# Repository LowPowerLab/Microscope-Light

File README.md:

# Microscope-Light
### Simple wireless ring light design for a B&amp;L stereo microscope

I designed this simple ring light because the commercially available solutions were bulky, required a separate power adapter, and I wanted something super compact and powered from a small LiPo battery.

Full video of making this is here: https://www.youtube.com/watch?v=bMRDT4bcLkU
Blog post here: https://lowpowerlab.com/2018/06/28/weekend-project-wireless-microscope-light-ring/

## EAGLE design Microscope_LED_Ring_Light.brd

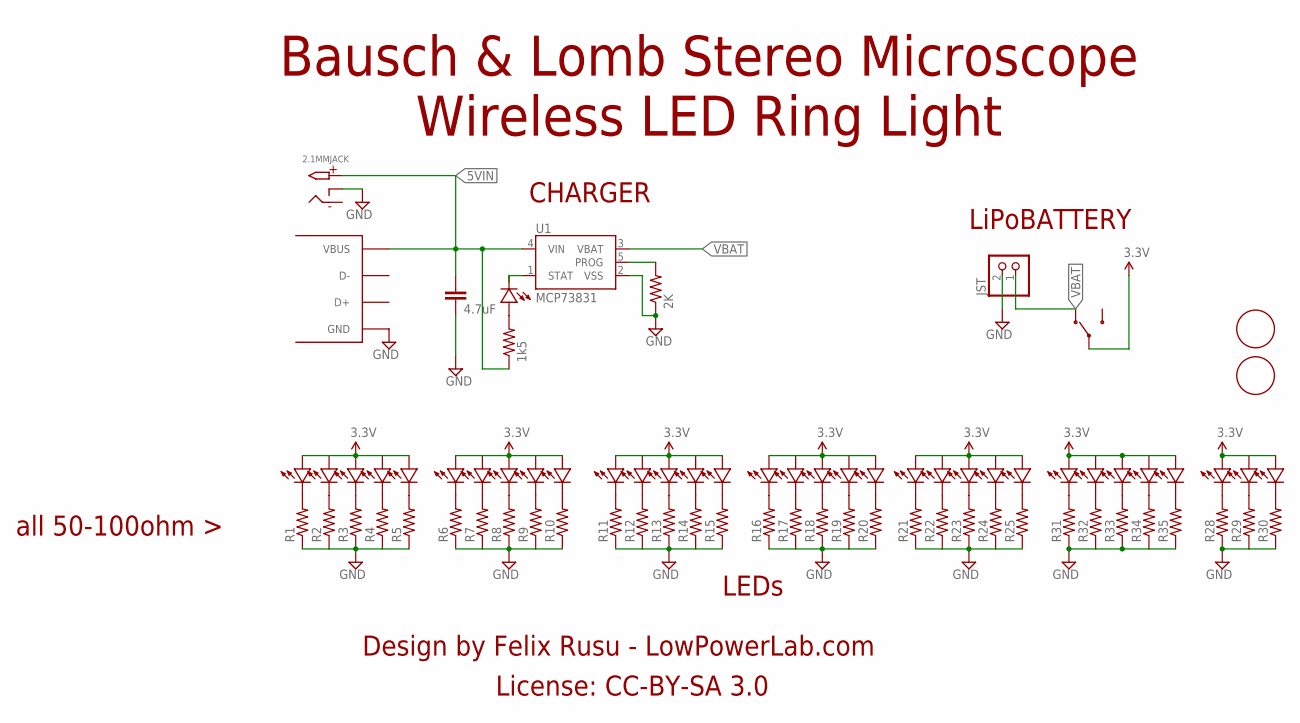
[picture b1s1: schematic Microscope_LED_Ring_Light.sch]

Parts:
2.1MMJACK: 2.1MMJACKSLOTS; 2.1MM_JACK_SLOTS
C1: 4.7uF; 0603-CAP
FIDUCIAL_BOTTOMRIGHT: FIDUCIAL1.5MM; FIDUCIAL_1.5MM
FIDUCIAL_TOPLEFT: FIDUCIAL1.5MM; FIDUCIAL_1.5MM
JST: JST_2PIN-SMT-RA; JST-PH-2-SMT-RA
R1, R2, R3, R4, R5, R6, R7, R8, R9, R10, R11, R12, R13, R14, R15, R16, R17, R18, R19, R20, R21, R22, R23, R24, R25, R28, R29, R30, R31, R32, R33, R34, R35: RESISTOR0805; 0805
R26: 1k5; 0603-RES
R27: 2K; 0603-RES
U1: MCP73831; SOT23-5
U$1, U$2, U$3, U$4, U$5, U$6, U$7, U$8, U$9, U$10, U$11, U$12, U$13, U$14, U$15, U$16, U$17, U$18, U$19, U$20, U$21, U$22, U$23, U$24, U$25, U$29, U$30, U$31, U$32, U$33, U$34, U$35, U$36: LED; LED_2.8X3.3MM
U$26: USB_4PIN2PINS_SLOTTED; USB-B-MICRO_2PADS_SLOTS
U$27: SWITCH_SPDT; SWITCH-SPDT_CKN9560
U$28: LED0603; 0603-LED

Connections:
3.3V: U$1.PLUS, U$2.PLUS, U$3.PLUS, U$4.PLUS, U$5.PLUS, U$6.PLUS, U$7.PLUS, U$8.PLUS, U$9.PLUS, U$10.PLUS, U$11.PLUS, U$12.PLUS, U$13.PLUS, U$14.PLUS, U$15.PLUS, U$16.PLUS, U$17.PLUS, U$18.PLUS, U$19.PLUS, U$20.PLUS, U$21.PLUS, U$22.PLUS, U$23.PLUS, U$24.PLUS, U$25.PLUS, U$27.2, U$29.PLUS, U$30.PLUS, U$31.PLUS, U$32.PLUS, U$33.PLUS, U$34.PLUS, U$35.PLUS, U$36.PLUS
5VIN: 2.1MMJACK.TIP, C1.1, R26.1, U1.4 (VIN), U$26.VBUS
GND: 2.1MMJACK.SIDE (RING_SW), C1.2, JST.2 (1), R1.1, R2.1, R3.1, R4.1, R5.1, R6.1, R7.1, R8.1, R9.1, R10.1, R11.1, R12.1, R13.1, R14.1, R15.1, R16.1, R17.1, R18.1, R19.1, R20.1, R21.1, R22.1, R23.1, R24.1, R25.1, R27.1, R28.1, R29.1, R30.1, R31.1, R32.1, R33.1, R34.1, R35.1, U1.2 (VSS), U$26.GND
unnamed: R1.2, U$3.MINUS
unnamed: R2.2, U$4.MINUS
unnamed: R3.2, U$5.MINUS
unnamed: R4.2, U$6.MINUS
unnamed: R5.2, U$7.MINUS
unnamed: R6.2, U$1.MINUS
unnamed: R7.2, U$2.MINUS
unnamed: R8.2, U$8.MINUS
unnamed: R9.2, U$9.MINUS
unnamed: R10.2, U$10.MINUS
unnamed: R11.2, U$11.MINUS
unnamed: R12.2, U$12.MINUS
unnamed: R13.2, U$13.MINUS
unnamed: R14.2, U$14.MINUS
unnamed: R15.2, U$15.MINUS
unnamed: R16.2, U$16.MINUS
unnamed: R17.2, U$17.MINUS
unnamed: R18.2, U$18.MINUS
unnamed: R19.2, U$19.MINUS
unnamed: R20.2, U$20.MINUS
unnamed: R21.2, U$21.MINUS
unnamed: R22.2, U$22.MINUS
unnamed: R23.2, U$23.MINUS
unnamed: R24.2, U$24.MINUS
unnamed: R25.2, U$25.MINUS
unnamed: R28.2, U$29.MINUS
unnamed: R26.2, U$28.PLUS
unnamed: R27.2, U1.5 (PROG)
unnamed: R29.2, U$30.MINUS
unnamed: R30.2, U$31.MINUS
unnamed: R31.2, U$32.MINUS
unnamed: R32.2, U$33.MINUS
unnamed: R33.2, U$34.MINUS
unnamed: R34.2, U$35.MINUS
unnamed: R35.2, U$36.MINUS
STAT: U1.1 (STAT), U$28.MINUS
VBAT: JST.1 (2), U1.3 (VBAT), U$27.1

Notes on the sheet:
CHARGER
LiPoBATTERY
LEDs
all 50-100ohm >
Design by Felix Rusu - LowPowerLab.com
License: CC-BY-SA 3.0
Bausch & Lomb Stereo Microscope Wireless LED Ring Light

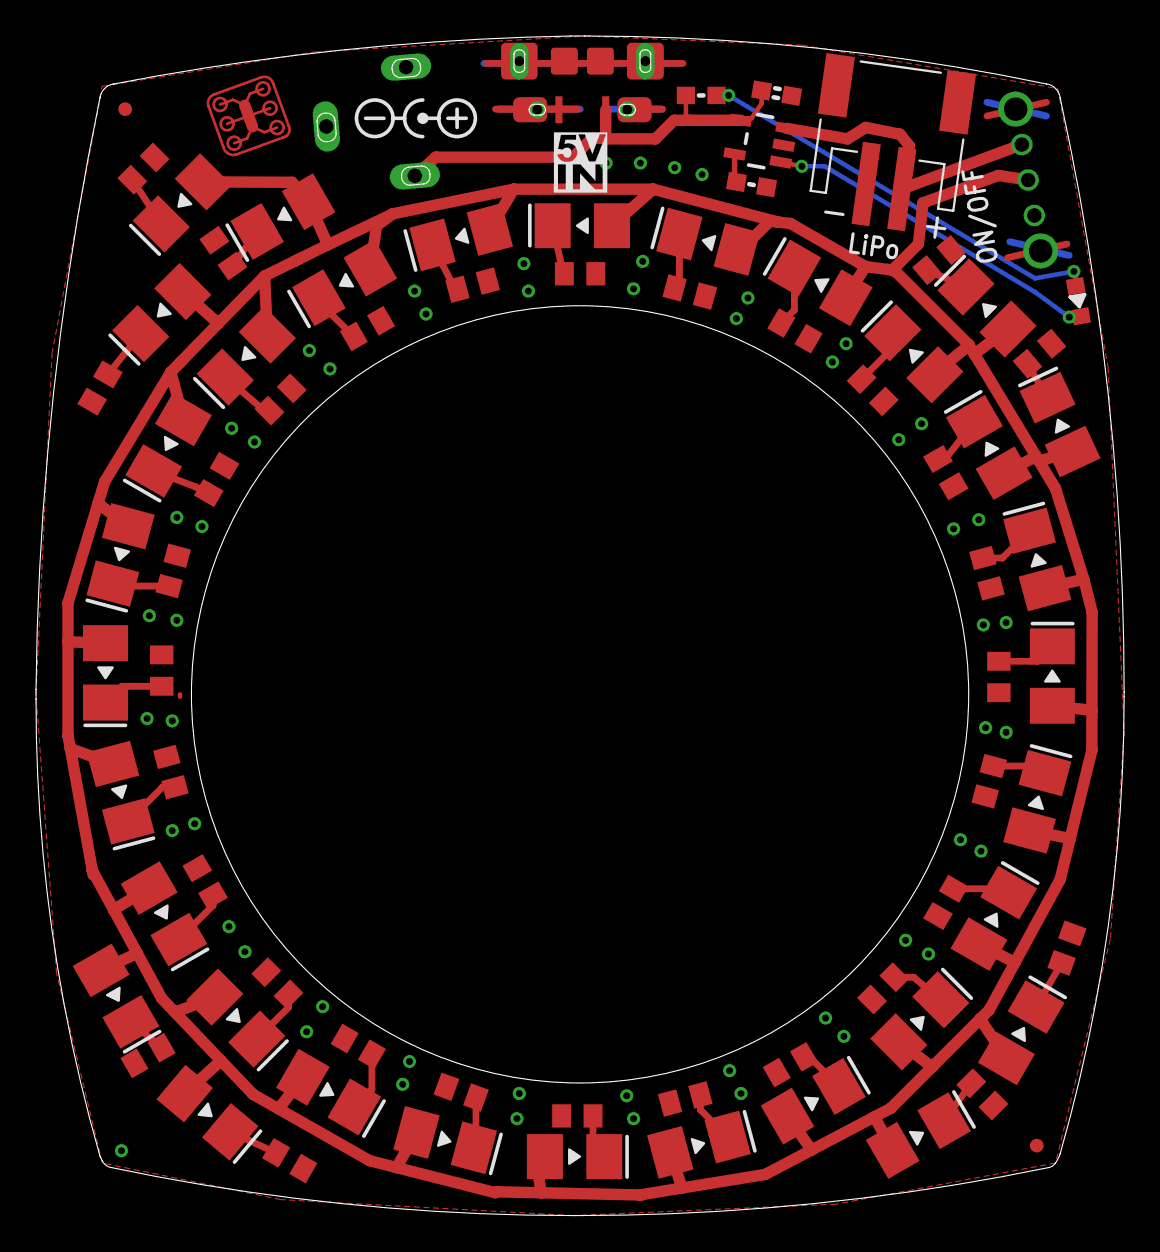
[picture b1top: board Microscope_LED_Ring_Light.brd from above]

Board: 2 copper layers, 60.5 x 65.5 mm, 81 parts (1 on the bottom side), 40 nets.

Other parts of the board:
U$37: LOGO_LOWPOWERLAB_COPPER
U$38: LOGO_LOWPOWERLAB_STOP
U$39: LOGO_5VIN
U$40: LOGO_LOWPOWERLAB

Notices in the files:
parts and their libraries:
SparkFun-Aesthetics: Licensing: Creative Commons ShareAlike 4.0 International - https://creativecommons.org/licenses/by-sa/4.0
